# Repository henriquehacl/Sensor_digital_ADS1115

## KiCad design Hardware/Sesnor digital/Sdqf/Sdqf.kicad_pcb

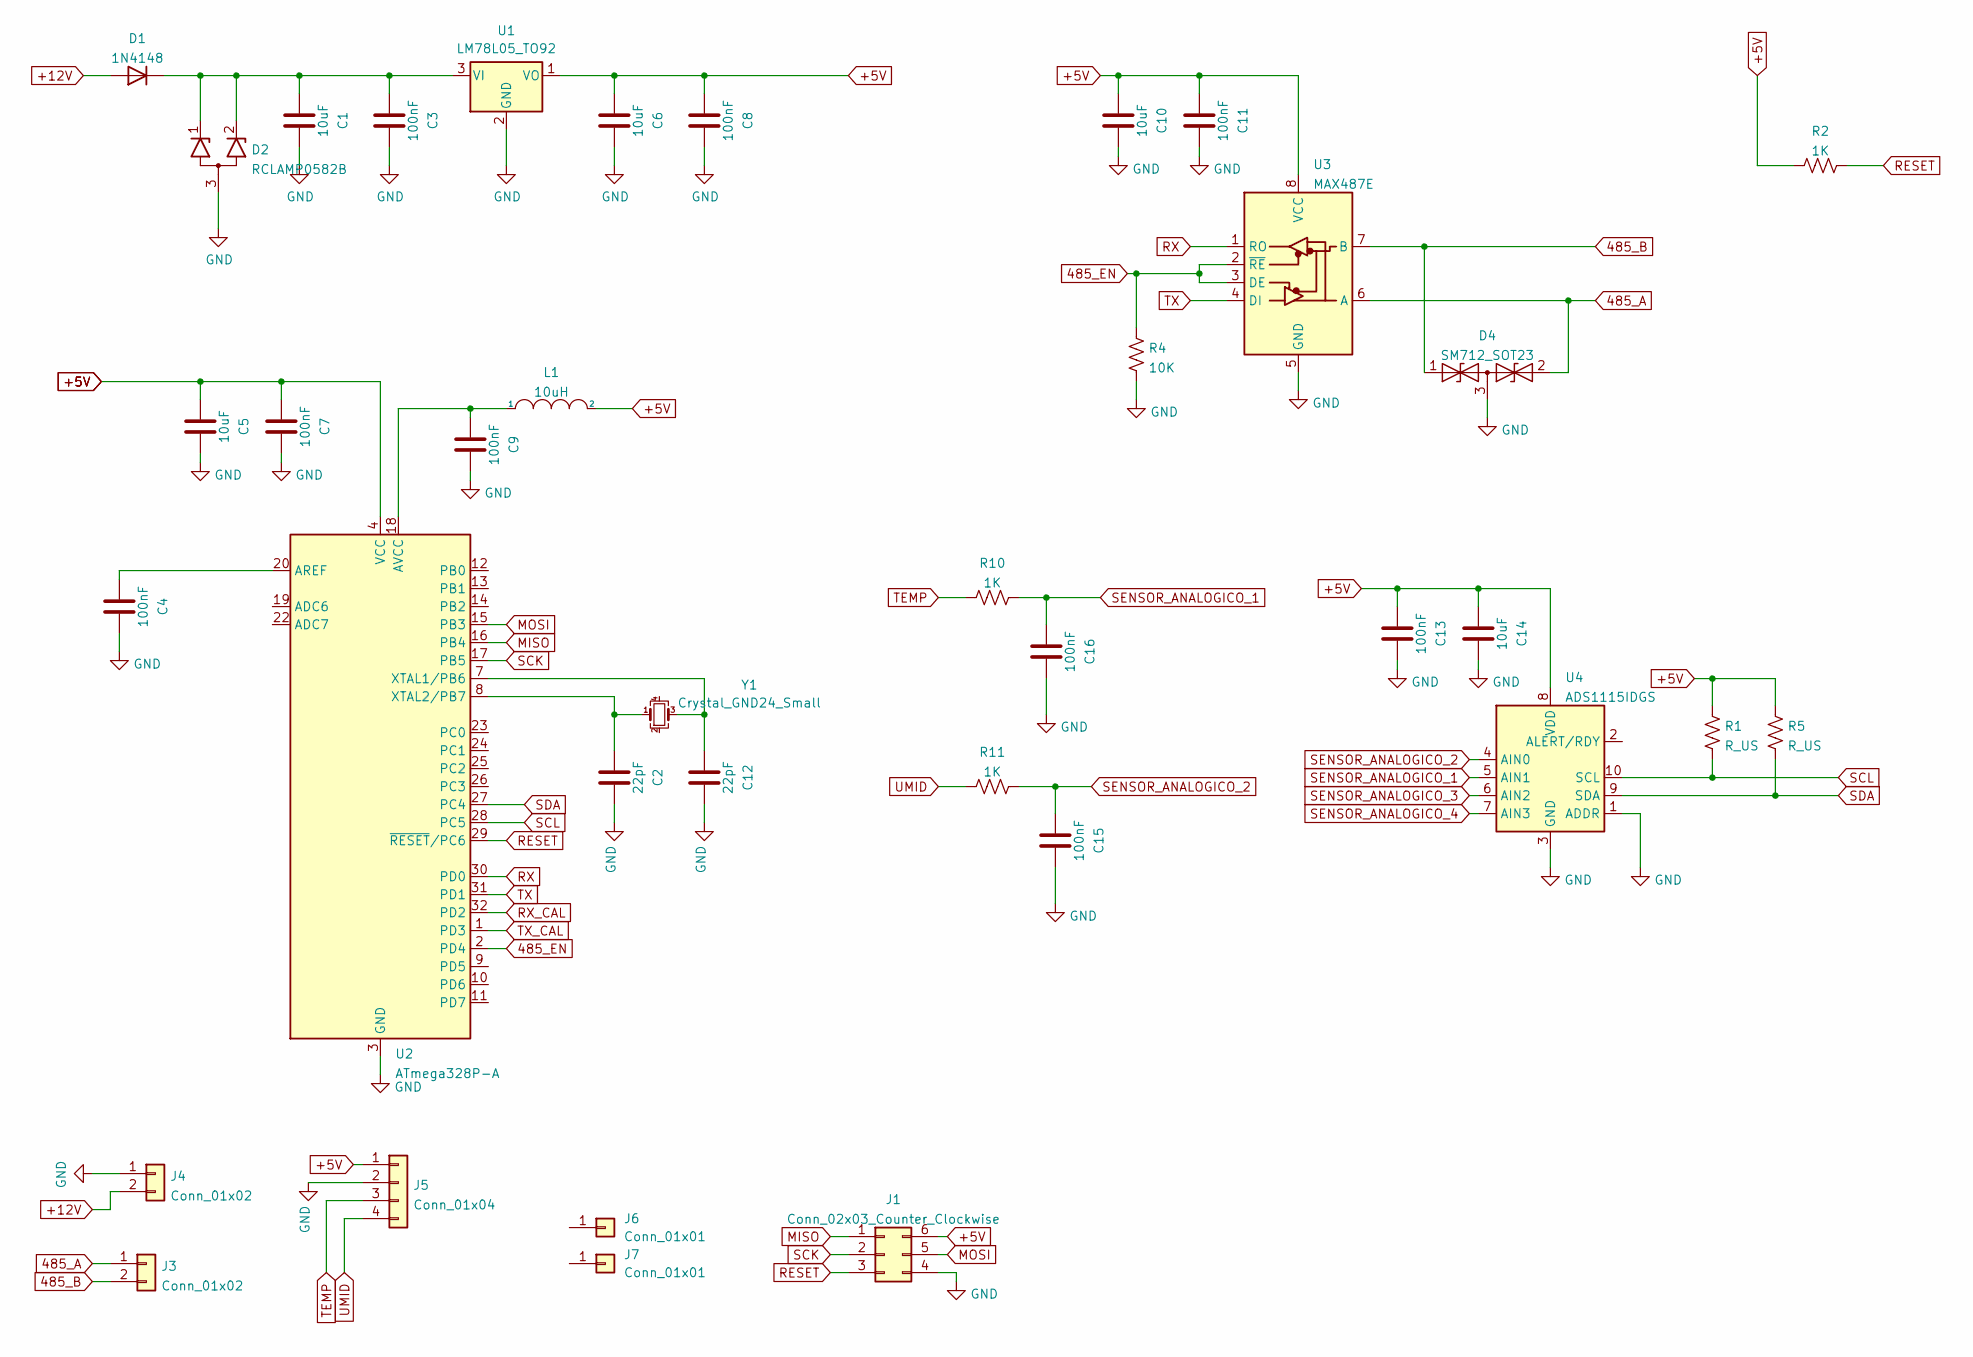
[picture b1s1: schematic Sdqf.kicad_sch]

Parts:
C1, C5, C6, C10, C14: 10uF; C_0805_2012Metric
C2, C12: 22pF; C_0603_1608Metric
C3, C4, C7, C8, C9, C11, C13, C15, C16: 100nF; C_0805_2012Metric
D1: 1N4148; D_SMA
D2: RCLAMP0582B; SOT-23
D4: SM712_SOT23; SOT-23
J1: Conn_02x03_Counter_Clockwise; PinHeader_2x03_P2.54mm_Vertical
J3, J4: Conn_01x02; TerminalBlock_Phoenix_MKDS-1,5-2-5.08_1x02_P5.08mm_Horizont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
J5: Conn_01x04; PinHeader_1x04_P2.54mm_Horizontal
J6, J7: Conn_01x01; MountingHole_2.7mm_M2.5
L1: 10uH; R_0805_2012Metric
R1, R5: R_US; R_0805_2012Metric
R2, R10, R11: 1K; R_0805_2012Metric
R4: 10K; R_0805_2012Metric
U1: LM78L05_TO92; TO-92_Inline
U2: ATmega328P-A; TQFP-32_7x7mm_P0.8mm
U3: MAX487E; SOIC-8_3.9x4.9mm_P1.27mm
U4: ADS1115IDGS; TSSOP-10_3x3mm_P0.5mm
Y1: Crystal_GND24_Small; Crystal_SMD_2016-4Pin_2.0x1.6mm

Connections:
485_A: D4.2 (A2), J3.1, U3.6 (A)
485_B: D4.1 (A1), J3.2, U3.7 (B)
485_EN: R4.2, U2.2 (PD4), U3.2 (~RE), U3.3 (DE)
+5V: C5.1, C6.1, C7.1, C8.1, C10.1, C11.1, C13.1, C14.1, J1.6, J5.1, L1.2, R1.1, R2.1, R5.1, U1.1 (VO), U2.4 (VCC), U2.6 (VCC), U3.8 (VCC), U4.8 (VDD)
+12V: D1.2 (A), J4.2
GND: C1.2, C2.2, C3.2, C4.2, C5.2, C6.2, C7.2, C8.2, C9.2, C10.2, C11.2, C12.2, C13.2, C14.2, C15.2, C16.2, D2.3 (A), D4.3 (common), J1.4, J4.1, J5.2, R4.1, U1.2 (GND), U2.3 (GND), U2.5 (GND), U2.21 (GND), U3.5 (GND), U4.1 (ADDR), U4.3 (GND)
MISO: J1.1, U2.16 (PB4)
MOSI: J1.5, U2.15 (PB3)
unnamed: C1.1, C3.1, D1.1 (K), D2.1 (K1), D2.2 (K2), U1.3 (VI)
unnamed: C4.1, U2.20 (AREF)
unnamed: C9.1, L1.1, U2.18 (AVCC)
unnamed: C12.1, U2.7 (XTAL1/PB6), Y1.3
unnamed: C2.1, U2.8 (XTAL2/PB7), Y1.1
RESET: J1.3, R2.2, U2.29 (~RESET/PC6)
RX: U2.30 (PD0), U3.1 (RO)
RX_CAL: U2.32 (PD2)
SCK: J1.2, U2.17 (PB5)
SCL: R1.2, U2.28 (PC5), U4.10 (SCL)
SDA: R5.2, U2.27 (PC4), U4.9 (SDA)
SENSOR_ANALOGICO_1: C16.1, R10.2, U4.5 (AIN1)
SENSOR_ANALOGICO_2: C15.1, R11.2, U4.4 (AIN0)
SENSOR_ANALOGICO_3: U4.6 (AIN2)
SENSOR_ANALOGICO_4: U4.7 (AIN3)
TEMP: J5.3, R10.1
TX: U2.31 (PD1), U3.4 (DI)
TX_CAL: U2.1 (PD3)
UMID: J5.4, R11.1

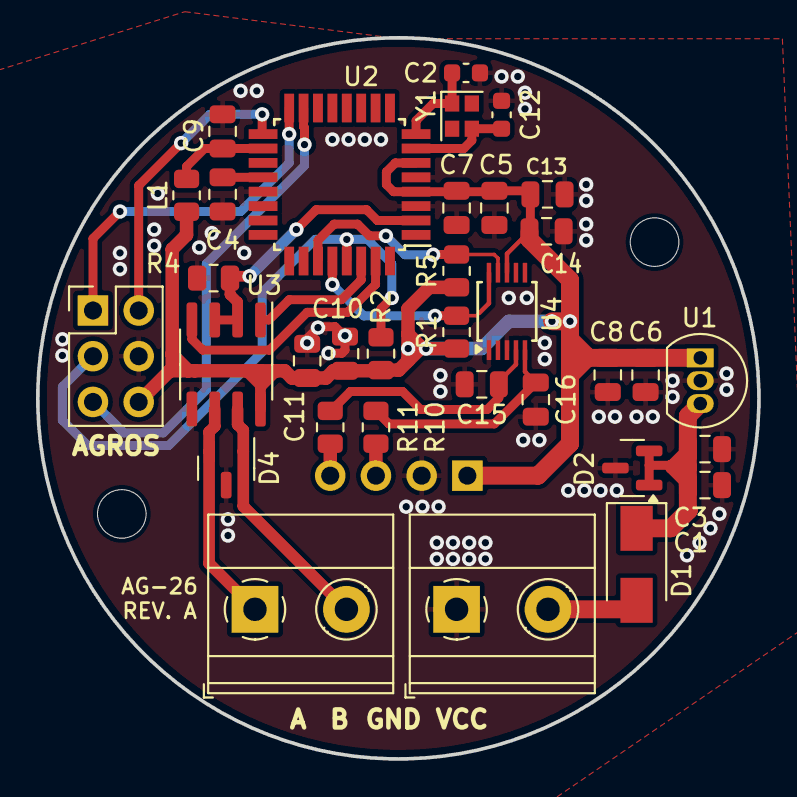
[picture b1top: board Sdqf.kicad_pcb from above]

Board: 2 copper layers, 40.1 x 40.1 mm, 37 parts (1 on the bottom side), 23 nets.

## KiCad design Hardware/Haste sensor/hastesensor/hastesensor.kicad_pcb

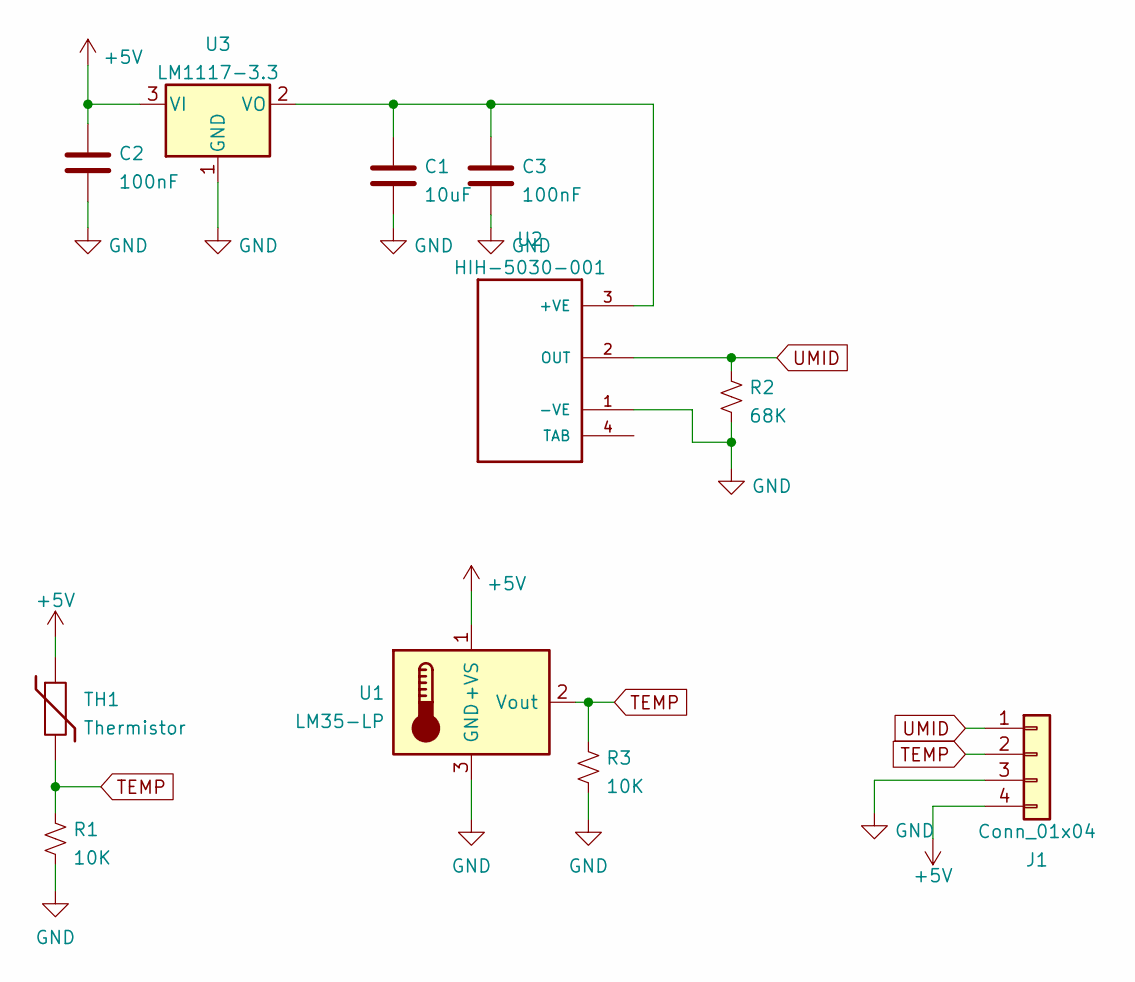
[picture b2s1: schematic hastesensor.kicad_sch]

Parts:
C1: 10uF; C_0805_2012Metric
C2, C3: 100nF; C_0805_2012Metric
J1: Conn_01x04; PinSocket_1x04_P2.54mm_Vertical
R1, R3: 10K; R_0805_2012Metric
R2: 68K; R_0805_2012Metric
TH1: Thermistor; R_Axial_DIN0204_L3.6mm_D1.6mm_P5.08mm_Horizontal
U1: LM35-LP; TO-92_Horizontal2
U2: HIH-5030-001; HONEYWELL_HIH-5030-001
U3: LM1117-3.3; SOT-223-3_TabPin2

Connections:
+5V: C2.1, J1.4, TH1.1, U1.1 (+VS), U3.3 (VI)
GND: C1.2, C2.2, C3.2, J1.3, R1.2, R2.2, R3.2, U1.3 (GND), U2.1 (-VE), U3.1 (GND)
unnamed: C1.1, C3.1, U2.3 (+VE), U3.2 (VO)
TEMP: J1.2, R1.1, R3.1, TH1.2, U1.2 (Vout)
UMID: J1.1, R2.1, U2.2 (OUT)

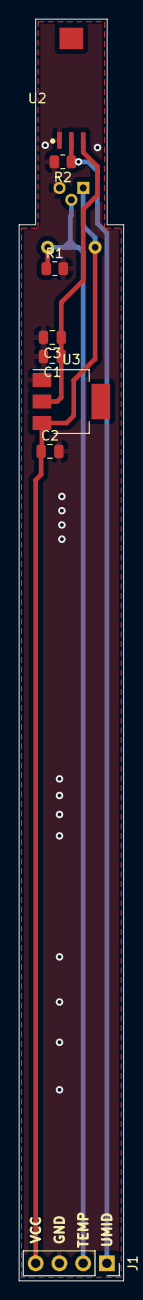
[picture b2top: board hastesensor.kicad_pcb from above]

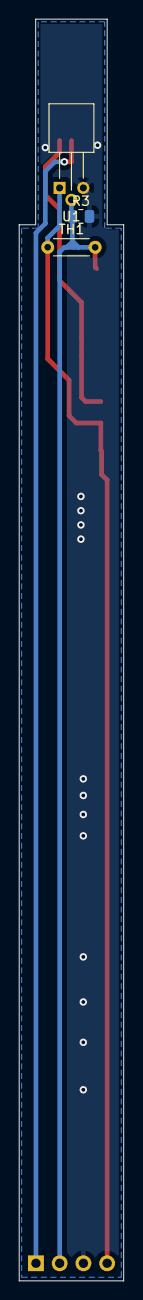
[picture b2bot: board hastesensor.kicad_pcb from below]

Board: 2 copper layers, 11.2 x 135.0 mm, 11 parts (3 on the bottom side), 5 nets.

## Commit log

2024-10-11 fdsaf
